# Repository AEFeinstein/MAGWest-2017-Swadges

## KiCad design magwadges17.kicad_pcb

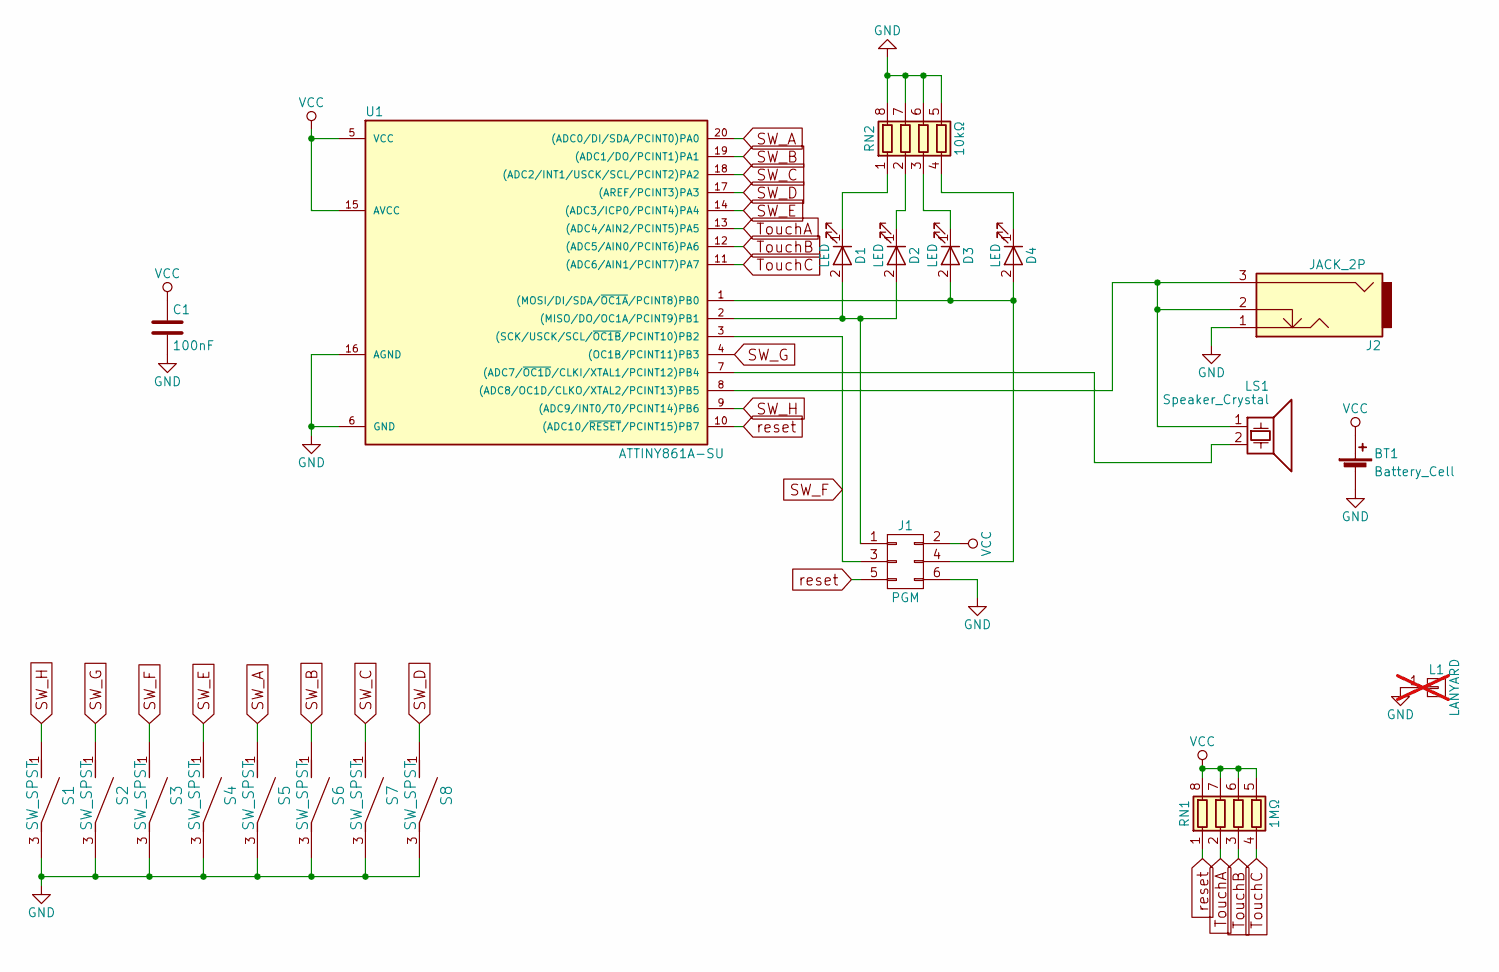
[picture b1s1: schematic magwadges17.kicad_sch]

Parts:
BT1: Battery_Cell; S8211-45R
C1: 100nF; C_0805_2012Metric; LCSC C38141
D1, D2, D3, D4: LED; LED_0805_2012Metric; LCSC C965817
J1: PGM; PinHeader_2x03_P2.54mm_Vertical_SMD; LCSC C3294461
J2: JACK_2P; SJ-252X-SMT
L1: LANYARD; 1pin; not fitted
LS1: Speaker_Crystal; PS1740P02CE; LCSC C129400
RN1: 1MΩ; R_Array_Concave_4x0603; LCSC C12038
RN2: 10kΩ; R_Array_Concave_4x0603; LCSC C29718
S1, S2, S3, S4, S5, S6, S7, S8: SW_SPST; SW_SPST_PTS645; LCSC C255812
U1: ATTINY861A-SU; SOIC-20W_7.5x12.8mm_P1.27mm; LCSC C94346

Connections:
GND: BT1.2 (-), C1.2, J1.6, J2.1, L1.1, RN2.5 (R4.2), RN2.6 (R3.2), RN2.7 (R2.2), RN2.8 (R1.2), S1.3, S2.3, S3.3, S4.3, S5.3, S6.3, S7.3, S8.3, U1.6 (GND), U1.16 (AGND)
unnamed: D1.2 (A), D2.2 (A), J1.1, U1.2 ((MISO/DO/OC1A/PCINT9)PB1)
unnamed: D1.1 (K), RN2.1 (R1.1)
unnamed: D2.1 (K), RN2.2 (R2.1)
unnamed: D3.2 (A), D4.2 (A), J1.4, U1.1 ((MOSI/DI/SDA/~OC1A/PCINT8)PB0)
unnamed: D3.1 (K), RN2.3 (R3.1)
unnamed: D4.1 (K), RN2.4 (R4.1)
unnamed: LS1.2, U1.7 ((ADC7/~OC1D/CLKI/XTAL1/PCINT12)PB4)
unnamed: J2.2, J2.3, LS1.1, U1.8 ((ADC8/OC1D/CLKO/XTAL2/PCINT13)PB5)
SW_A: S5.1, U1.20 ((ADC0/DI/SDA/PCINT0)PA0)
SW_B: S6.1, U1.19 ((ADC1/DO/PCINT1)PA1)
SW_C: S7.1, U1.18 ((ADC2/INT1/USCK/SCL/PCINT2)PA2)
SW_D: S8.1, U1.17 ((AREF/PCINT3)PA3)
SW_E: S4.1, U1.14 ((ADC3/ICP0/PCINT4)PA4)
SW_F: J1.3, S3.1, U1.3 ((SCK/USCK/SCL/~OC1B/PCINT10)PB2)
SW_G: S2.1, U1.4 ((OC1B/PCINT11)PB3)
SW_H: S1.1, U1.9 ((ADC9/INT0/T0/PCINT14)PB6)
TouchA: RN1.2 (R2.1), U1.13 ((ADC4/AIN2/PCINT5)PA5)
TouchB: RN1.3 (R3.1), U1.12 ((ADC5/AIN0/PCINT6)PA6)
TouchC: RN1.4 (R4.1), U1.11 ((ADC6/AIN1/PCINT7)PA7)
VCC: BT1.1 (+), C1.1, J1.2, RN1.5 (R4.2), RN1.6 (R3.2), RN1.7 (R2.2), RN1.8 (R1.2), U1.5 (VCC), U1.15 (AVCC)
reset: J1.5, RN1.1 (R1.1), U1.10 ((ADC10/~RESET/PCINT15)PB7)

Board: 2 copper layers, 34 parts (7 on the bottom side), 22 nets, no tracks yet.

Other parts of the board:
G0, G1, G2, G4, G4#2, G5, G6, G7, G8, G9, G11, G12, G13: LOGO; test_star4

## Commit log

2024-03-12 Start to add LCSC parts
2024-03-15 Clean up board, rip traces
